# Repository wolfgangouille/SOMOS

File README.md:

# SOMOS
Contains all assets for SOMOS

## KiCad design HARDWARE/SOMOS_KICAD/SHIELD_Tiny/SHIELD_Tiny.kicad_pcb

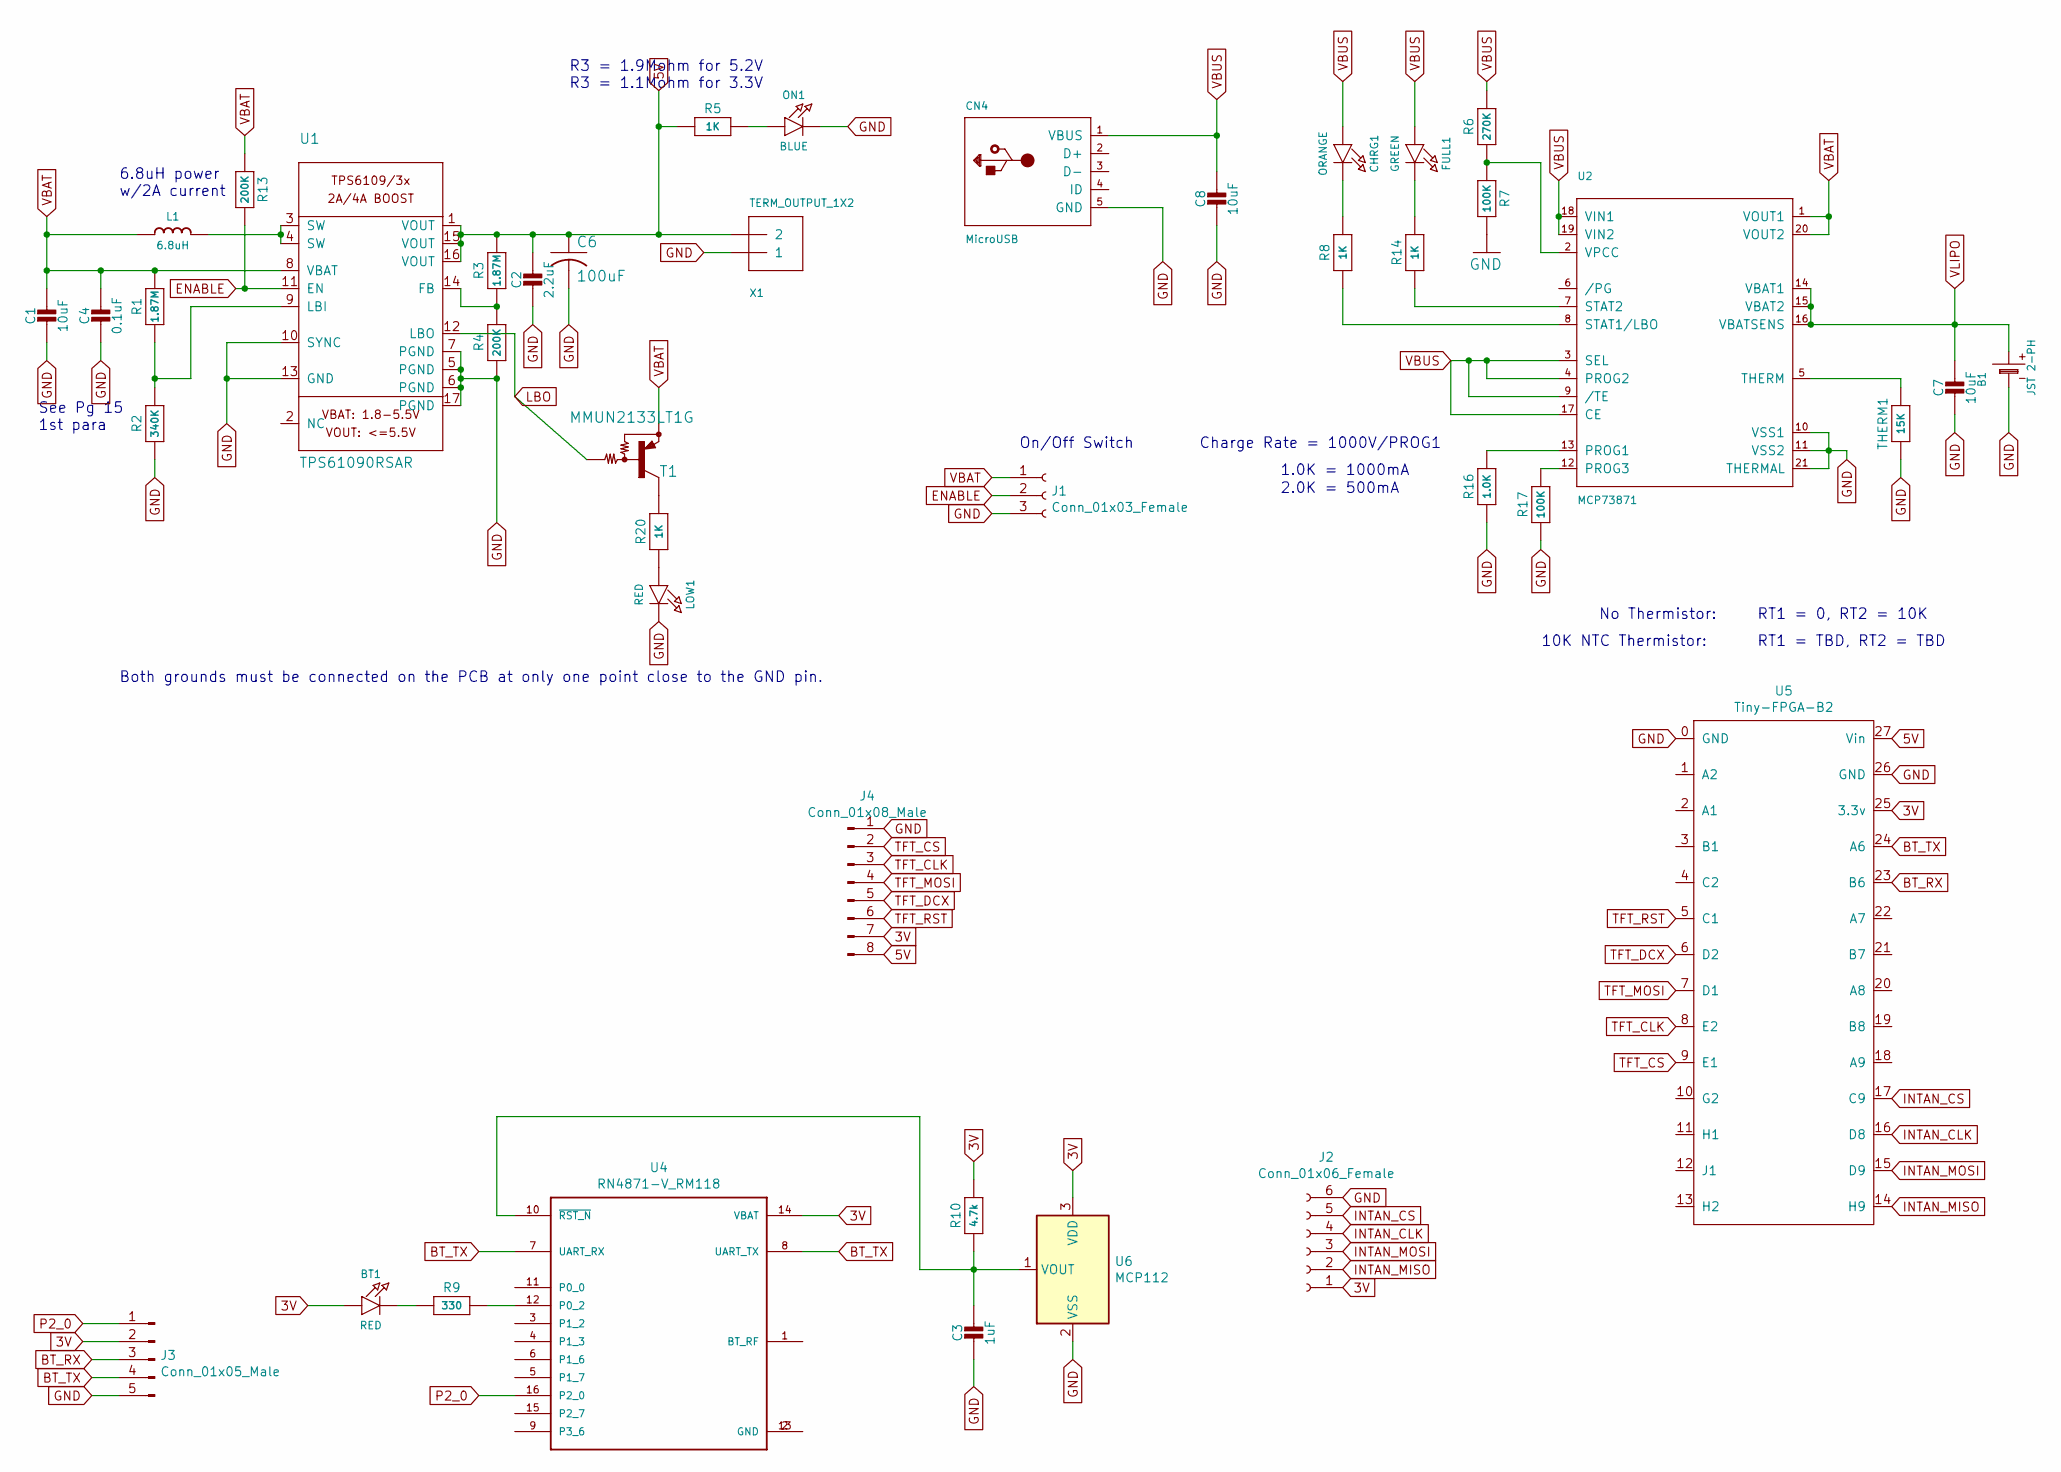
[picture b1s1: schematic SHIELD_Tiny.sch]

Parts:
B1: JST 2-PH; PinHeader_1x02_P2.54mm_Vertical
BT1: RED; LED_0603_1608Metric_Castellated
C1, C7, C8: 10uF; C_0805_2012Metric
C2: 2.2uF; C_0805_2012Metric
C3: 1uF; C_0805_2012Metric
C4: 0.1uF; C_0805_2012Metric
C6: 100uF; C_1210_3225Metric
CHRG1: ORANGE; LED_0603_1608Metric_Castellated
CN4: MicroUSB; USB_Micro-B_GCT_USB3076-30-A
FULL1: GREEN; LED_0603_1608Metric_Castellated
J1: Conn_01x03_Female; PinHeader_1x03_P2.54mm_Vertical
J2: Conn_01x06_Female; JST_SH_SM06B-SRSS-TB_1x06-1MP_P1.00mm_Horizontal
J3: Conn_01x05_Male; JST_SH_SM05B-SRSS-TB_1x05-1MP_P1.00mm_Horizontal
J4: Conn_01x08_Male; JST_SH_SM08B-SRSS-TB_1x08-1MP_P1.00mm_Horizontal
L1: 6.8uH; L_Wuerth_WE-PD2-Typ-MS
LOW1: RED; LED_0603_1608Metric_Castellated
ON1: BLUE; LED_0603_1608Metric_Castellated
R1, R3: 1.87M; R_0805_2012Metric
R2: 340K; R_0805_2012Metric
R4, R13: 200K; R_0805_2012Metric
R5, R8, R14, R20: 1K; R_0603_1608Metric
R6: 270K; R_0805_2012Metric
R7, R17: 100K; R_0603_1608Metric
R9: 330; R_0603_1608Metric
R10: 4.7k; R_0603_1608Metric
R16: 1.0K; R_0603_1608Metric
T1: MMUN2133LT1G; SOT-23
THERM1: 15K; R_0805_2012Metric
U1: TPS61090RSAR; QFN-16-1EP_4x4mm_P0.65mm_EP2.7x2.7mm_ThermalVias
U2: MCP73871; Texas_S-PVQFN-N20_EP2.4x2.4mm_ThermalVias
U4: RN4871-V_RM118; RN4871
U5: Tiny-FPGA-B2; TinyFPGA-BX_TH
U6: MCP112; TO-92_Inline
X1: TERM_OUTPUT_1X2; PinHeader_1x02_P2.54mm_Vertical

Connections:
3V: BT1.1 (A), J2.1, J3.2, J4.7, R10.2, U4.14 (VBAT), U5.25 (3.3v), U6.3 (VDD)
5V: C2.1, C6.1, J4.8, R3.2, R5.1, U1.1 (VOUT), U1.15 (VOUT), U1.16 (VOUT), U5.27 (Vin), X1.2
BT_RX: J3.3, U5.23 (B6)
BT_TX: J3.4, U4.7 (UART_RX), U4.8 (UART_TX), U5.24 (A6)
ENABLE: J1.2, R13.2, U1.11 (EN)
GND: B1.1 (-), C1.2, C2.2, C3.2, C4.2, C6.2, C7.2, C8.2, CN4.5 (GND), CN4.6 (GND), J1.3, J2.6, J3.5, J4.1, LOW1.2 (C), ON1.2 (C), R2.1, R4.1, R7.2, R16.1, R17.1, THERM1.1, U1.5 (PGND), U1.6 (PGND), U1.7 (PGND), U1.10 (SYNC), U1.13 (GND), U1.17 (PGND), U2.10 (VSS1), U2.11 (VSS2), U2.21 (THERMAL), U5.0 (GND), U5.26 (GND), U6.2 (VSS), X1.1
INTAN_CLK: J2.4, U5.16 (D8)
INTAN_CS: J2.5, U5.17 (C9)
INTAN_MISO: J2.2, U5.14 (H9)
INTAN_MOSI: J2.3, U5.15 (D9)
LBO: T1.1 (B), U1.12 (LBO)
unnamed: BT1.2 (C), R9.1
unnamed: C3.1, R10.1, U4.10 (~RST_N~), U6.1 (VOUT)
unnamed: CHRG1.2 (C), R8.2
unnamed: FULL1.2 (C), R14.2
unnamed: L1.2, U1.3 (SW), U1.4 (SW)
unnamed: LOW1.1 (A), R20.1
unnamed: ON1.1 (A), R5.2
unnamed: R1.1, R2.2, U1.9 (LBI)
unnamed: R3.1, R4.2, U1.14 (FB)
unnamed: R6.1, R7.1, U2.2 (VPCC)
unnamed: R8.1, U2.8 (STAT1/LBO)
unnamed: R9.2, U4.12 (P0_2)
unnamed: R14.1, U2.7 (STAT2)
unnamed: R16.2, U2.13 (PROG1)
unnamed: R17.2, U2.12 (PROG3)
unnamed: R20.2, T1.3 (C)
unnamed: THERM1.2, U2.5 (THERM)
unnamed: U4.2 (GND), U4.13 (GND)
P2_0: J3.1, U4.16 (P2_0)
TFT_CLK: J4.3, U5.8 (E2)
TFT_CS: J4.2, U5.9 (E1)
TFT_DCX: J4.5, U5.6 (D2)
TFT_MOSI: J4.4, U5.7 (D1)
TFT_RST: J4.6, U5.5 (C1)
VBAT: C1.1, C4.1, J1.1, L1.1, R1.2, R13.1, T1.2 (E), U1.8 (VBAT), U2.1 (VOUT1), U2.20 (VOUT2)
VBUS: C8.1, CHRG1.1 (A), CN4.1 (VBUS), FULL1.1 (A), R6.2, U2.3 (SEL), U2.4 (PROG2), U2.9 (/TE), U2.17 (CE), U2.18 (VIN1), U2.19 (VIN2)
VLIPO: B1.2 (+), C7.1, U2.14 (VBAT1), U2.15 (VBAT2), U2.16 (VBATSENS)

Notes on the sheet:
On/Off Switch
RT1 = TBD, RT2 = TBD
RT1 = 0, RT2 = 10K
10K NTC Thermistor:
No Thermistor:
2.0K = 500mA
1.0K = 1000mA
Charge Rate = 1000V/PROG1
R3 = 1.9Mohm for 5.2V R3 = 1.1Mohm for 3.3V
6.8uH power w/2A current
See Pg 15 1st para
Both grounds must be connected on the PCB at only one point close to the GND pin.

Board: 2 copper layers, 42 parts (28 on the bottom side), 38 nets, no tracks yet.

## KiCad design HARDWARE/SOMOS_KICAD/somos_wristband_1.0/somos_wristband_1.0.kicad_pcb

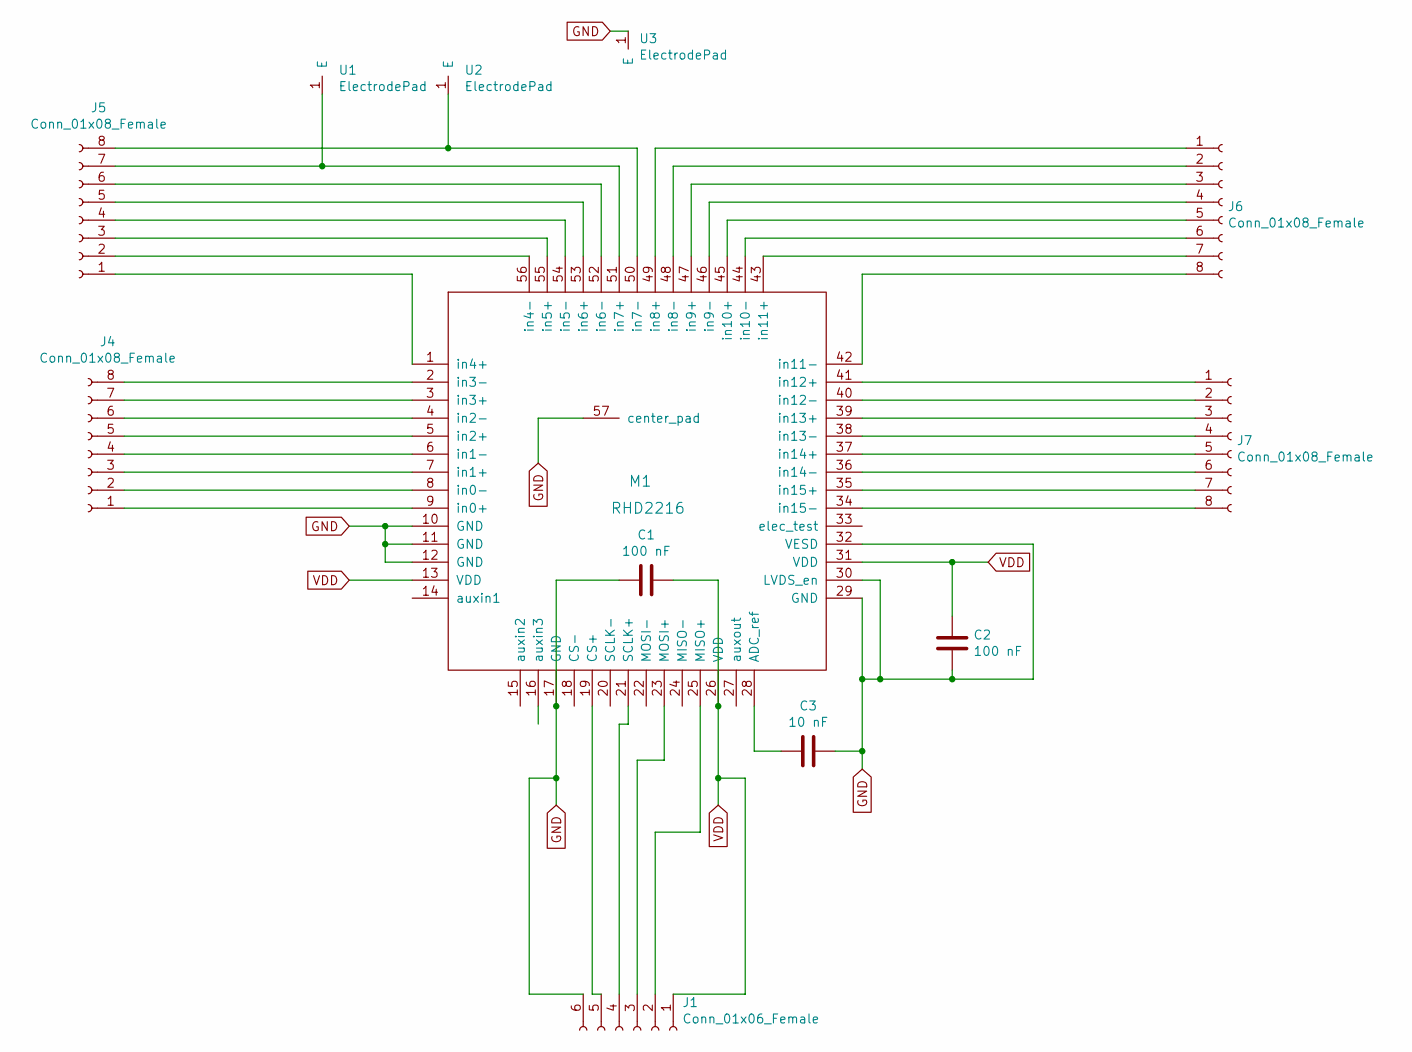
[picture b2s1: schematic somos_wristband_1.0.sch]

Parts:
C1, C2: 100 nF; C_0402_1005Metric
C3: 10 nF; C_0402_1005Metric
J1: Conn_01x06_Female; PinHeader_2x03_P2.54mm_Horizontal
J4, J5, J6, J7: Conn_01x08_Female; PinHeader_1x08_P2.54mm_Vertical
M1: RHD2216; RHD2216_QFN56
U1, U2, U3: ElectrodePad; SOMOS_ELECTRODE

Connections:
GND: C1.2, C2.1, C3.2, J1.6, M1.10 (GND), M1.11 (GND), M1.12 (GND), M1.17 (GND), M1.29 (GND), M1.30 (LVDS_en), M1.32 (VESD), M1.57 (center_pad), U3.1
unnamed: C3.1, M1.28 (ADC_ref)
unnamed: J1.2, M1.25 (MISO+)
unnamed: J1.3, M1.23 (MOSI+)
unnamed: J1.4, M1.21 (SCLK+)
unnamed: J1.5, M1.19 (CS+)
unnamed: J4.1, M1.9 (in0+)
unnamed: J4.2, M1.8 (in0-)
unnamed: J4.3, M1.7 (in1+)
unnamed: J4.4, M1.6 (in1-)
unnamed: J4.5, M1.5 (in2+)
unnamed: J4.6, M1.4 (in2-)
unnamed: J4.7, M1.3 (in3+)
unnamed: J4.8, M1.2 (in3-)
unnamed: J5.1, M1.1 (in4+)
unnamed: J5.2, M1.56 (in4-)
unnamed: J5.3, M1.55 (in5+)
unnamed: J5.4, M1.54 (in5-)
unnamed: J5.5, M1.53 (in6+)
unnamed: J5.6, M1.52 (in6-)
unnamed: J5.7, M1.51 (in7+), U1.1
unnamed: J5.8, M1.50 (in7-), U2.1
unnamed: J6.1, M1.49 (in8+)
unnamed: J6.2, M1.48 (in8-)
unnamed: J6.3, M1.47 (in9+)
unnamed: J6.4, M1.46 (in9-)
unnamed: J6.5, M1.45 (in10+)
unnamed: J6.6, M1.44 (in10-)
unnamed: J6.7, M1.43 (in11+)
unnamed: J6.8, M1.42 (in11-)
unnamed: J7.1, M1.41 (in12+)
unnamed: J7.2, M1.40 (in12-)
unnamed: J7.3, M1.39 (in13+)
unnamed: J7.4, M1.38 (in13-)
unnamed: J7.5, M1.37 (in14+)
unnamed: J7.6, M1.36 (in14-)
unnamed: J7.7, M1.35 (in15+)
unnamed: J7.8, M1.34 (in15-)
VDD: C1.1, C2.2, J1.1, M1.13 (VDD), M1.26 (VDD), M1.31 (VDD)

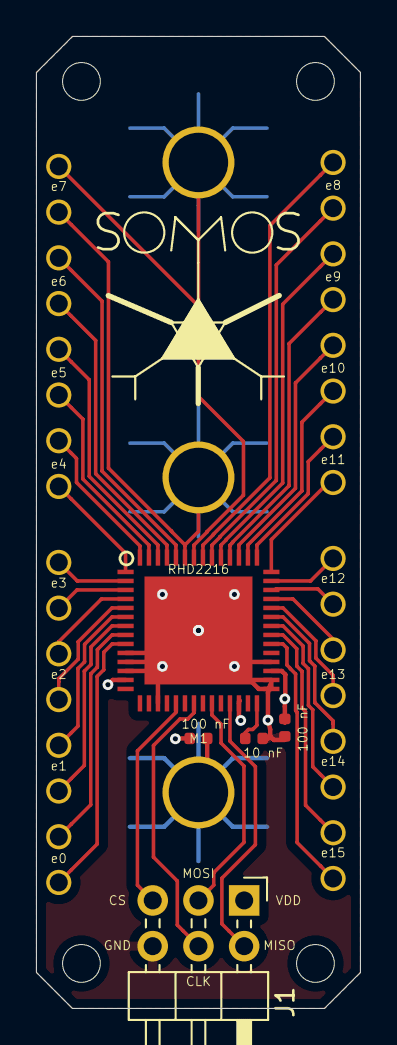
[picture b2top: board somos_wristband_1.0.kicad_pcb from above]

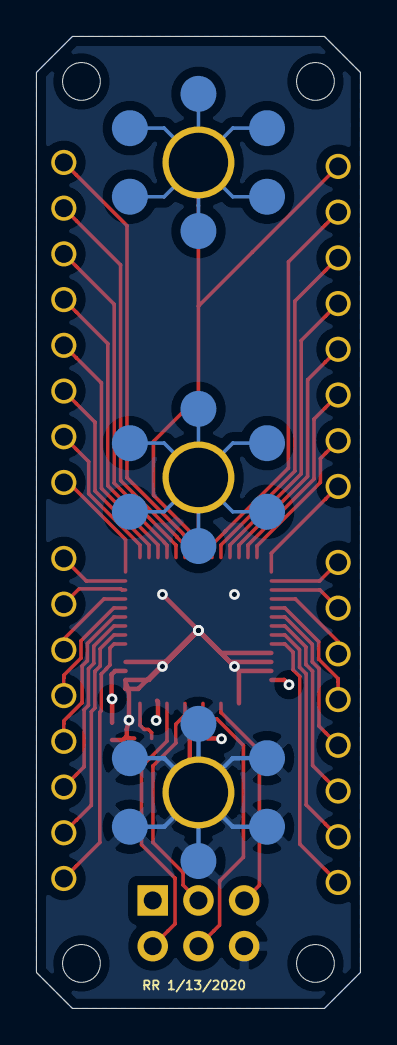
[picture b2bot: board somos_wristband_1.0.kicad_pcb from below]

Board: 4 copper layers, 18.0 x 54.0 mm, 12 parts (3 on the bottom side), 39 nets.

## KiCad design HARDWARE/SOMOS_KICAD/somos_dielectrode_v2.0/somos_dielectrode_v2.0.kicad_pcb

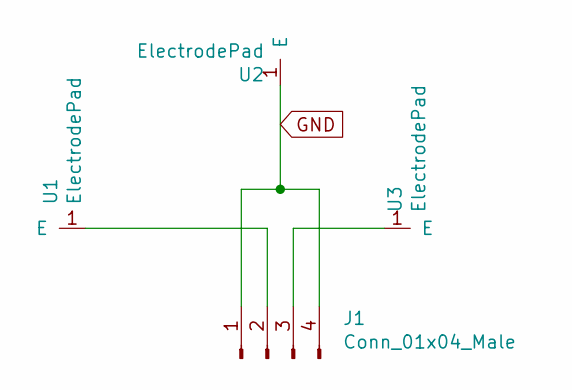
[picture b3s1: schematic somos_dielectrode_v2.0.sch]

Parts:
J1: Conn_01x04_Male; JST_SH_SM04B-SRSS-TB_1x04-DUAL
U1, U2, U3: ElectrodePad; SOMOS_ELECTRODE_2

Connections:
GND: J1.1, J1.4, U2.1
unnamed: J1.2, U1.1
unnamed: J1.3, U3.1

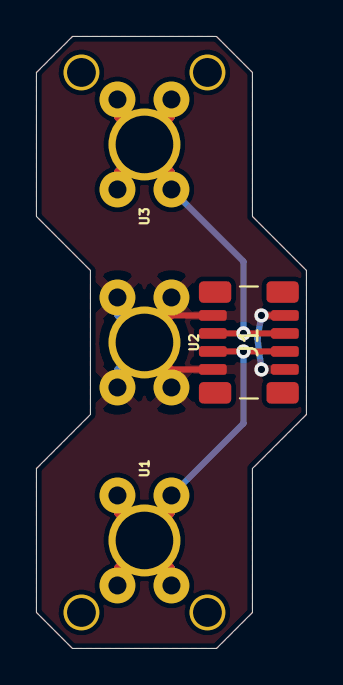
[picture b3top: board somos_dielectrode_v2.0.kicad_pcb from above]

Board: 2 copper layers, 15.0 x 34.0 mm, 4 parts (0 on the bottom side), 3 nets.

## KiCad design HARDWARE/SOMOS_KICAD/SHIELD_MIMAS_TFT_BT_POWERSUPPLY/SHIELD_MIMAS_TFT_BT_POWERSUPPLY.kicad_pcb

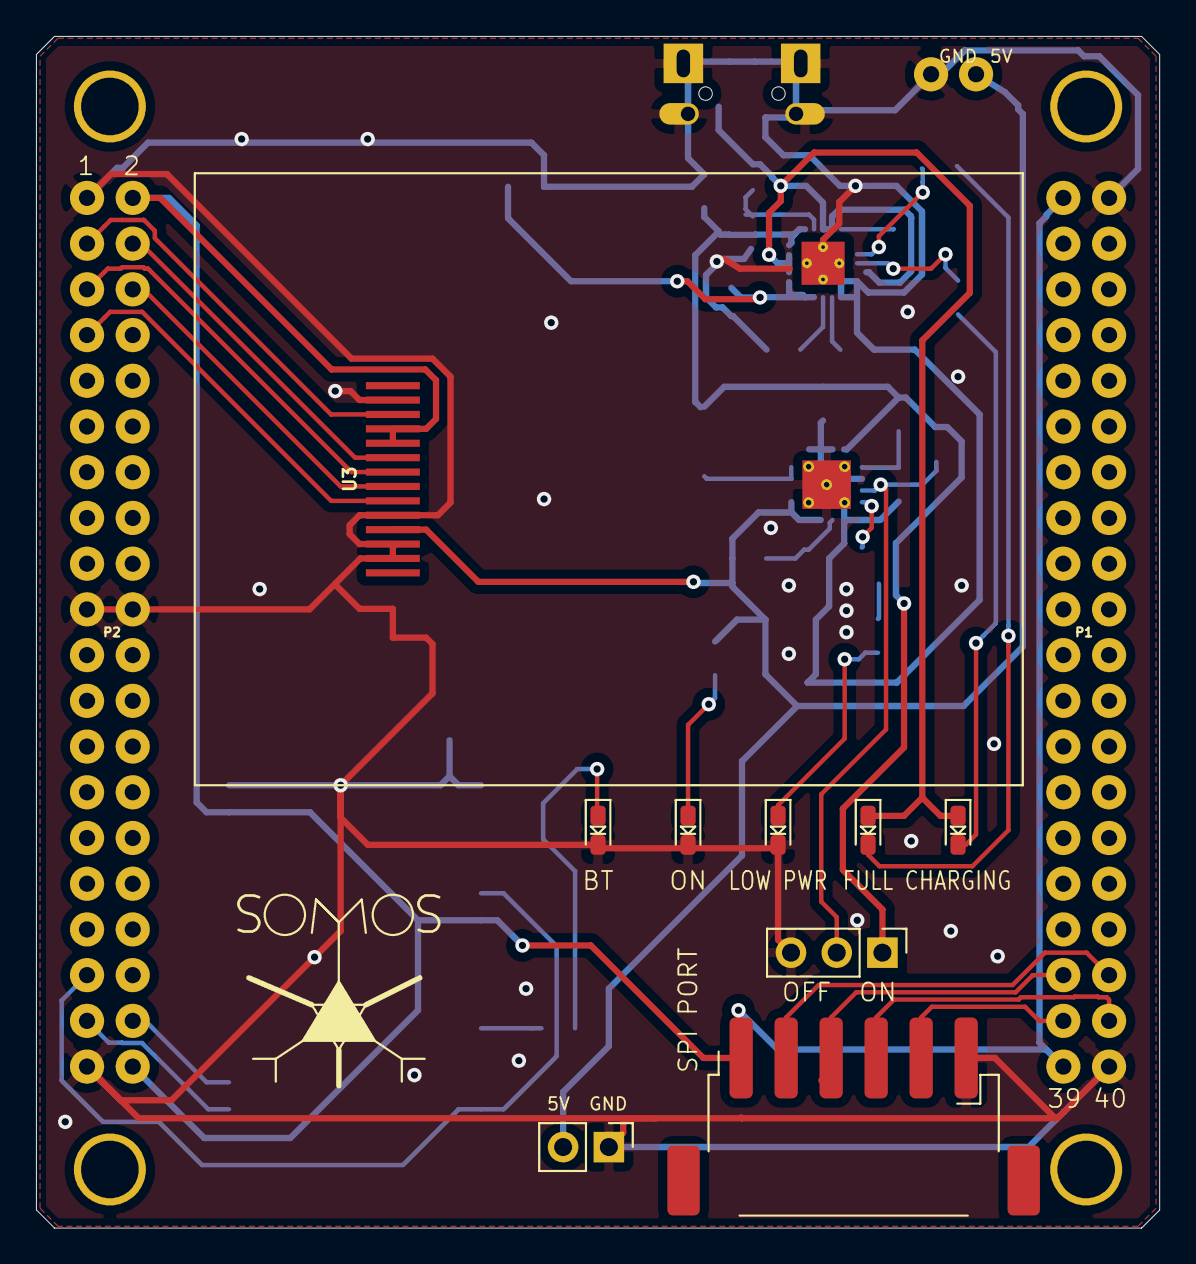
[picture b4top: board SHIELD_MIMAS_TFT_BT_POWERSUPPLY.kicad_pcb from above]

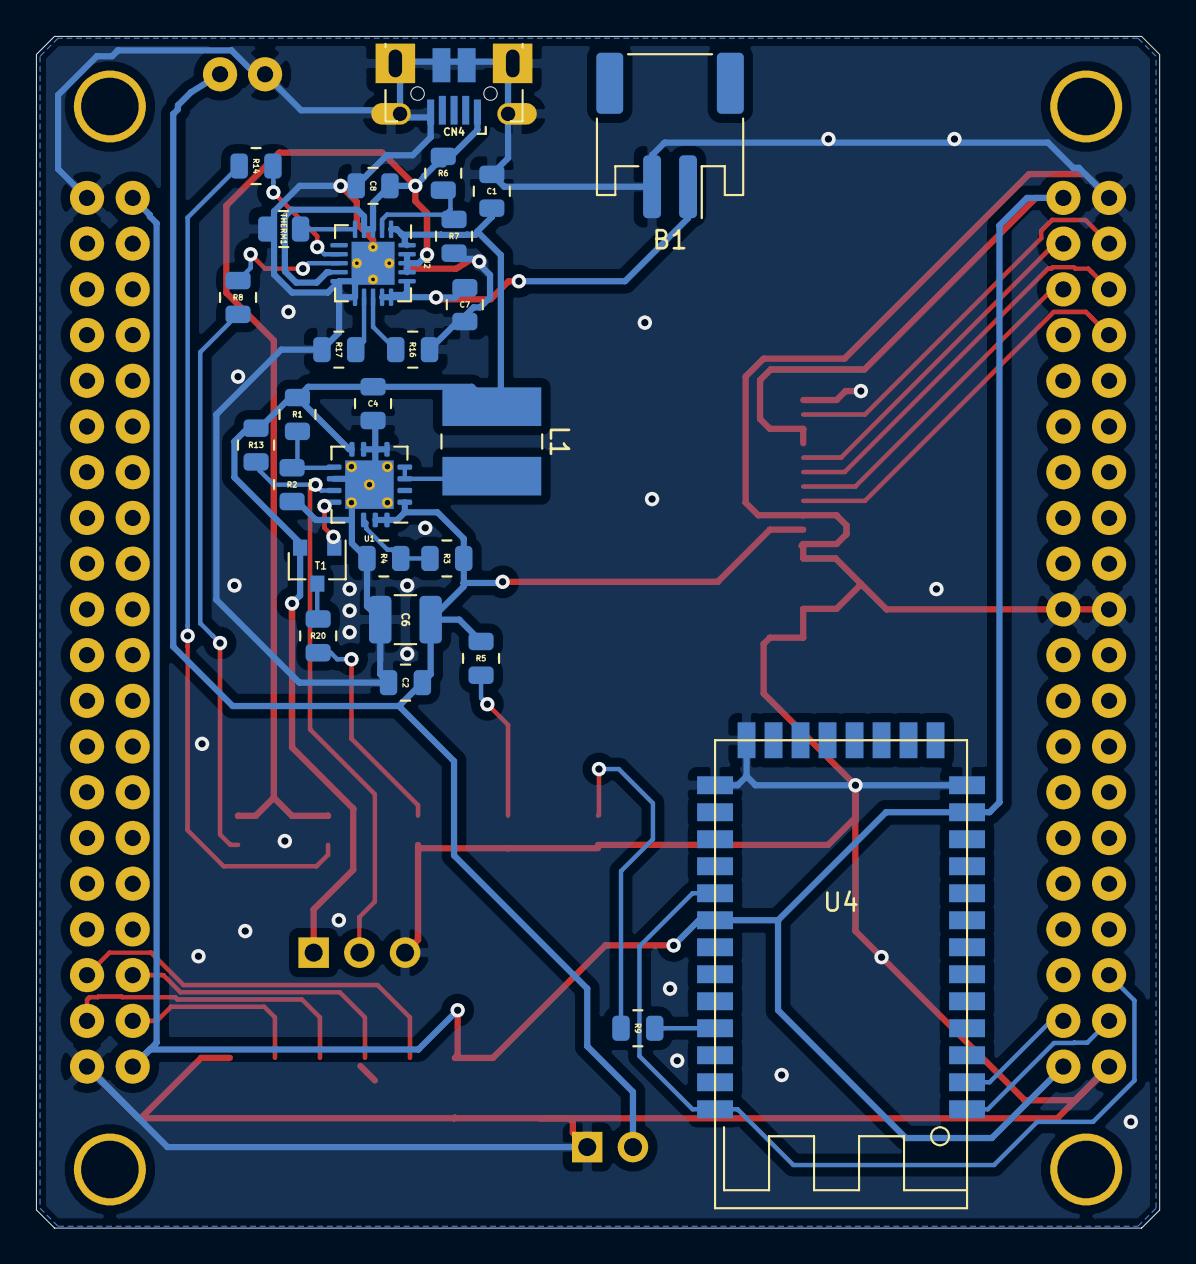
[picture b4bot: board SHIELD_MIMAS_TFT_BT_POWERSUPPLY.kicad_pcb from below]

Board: 2 copper layers, 62.4 x 66.2 mm, 38 parts (28 on the bottom side), 36 nets.

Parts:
5V  GND: TERM_OUTPUT_1X2; PinHeader_1x02_P2.54mm_Vertical
B1: JST 2-PH; JST_PH_S2B-PH-SM4-TB_1x02-1MP_P2.00mm_Horizontal
BT: RED; LED_0603_1608Metric_Castellated
C1, C7, C8: 10uF; C_0805_2012Metric
C2: 2.2uF; C_0805_2012Metric
C4: 0.1uF; C_0805_2012Metric
C6: 100uF; C_1210_3225Metric
CHARGING: ORANGE; LED_0603_1608Metric_Castellated
CN4: MicroUSB; USB_Micro-B_GCT_USB3076-30-A
FULL: GREEN; LED_0603_1608Metric_Castellated
L1: 6.8uH; L_Wuerth_WE-PD2-Typ-MS
LOW PWR: RED; LED_0603_1608Metric_Castellated
OFF  ON: Conn_01x03_Female; PinHeader_1x03_P2.54mm_Vertical
ON: BLUE; LED_0603_1608Metric_Castellated
P1: CONN_40X2; MIMAS_mountingholes
R1, R3: 1.87M; R_0805_2012Metric
R2: 340K; R_0805_2012Metric
R4, R13: 200K; R_0805_2012Metric
R5, R8, R9, R14, R20: 1K; R_0805_2012Metric
R6: 270K; R_0805_2012Metric
R7, R17: 100K; R_0805_2012Metric
R16: 1.0K; R_0805_2012Metric
SPI PORT: Conn_01x06_Female; JST_XH_S6B-XH-SM4
T1: MMUN2133LT1G; SOT-23
THERM1: 15K; R_0805_2012Metric
U1: TPS61090RSAR; QFN-16-1EP_4x4mm_P0.65mm_EP2.7x2.7mm_ThermalVias
U2: MCP73871; Texas_S-PVQFN-N20_EP2.4x2.4mm_ThermalVias
U3: TFT_128x160; TFT128x160
U4: HC-05; HC-05_SMC

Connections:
3V: P1.1-1, P1.1-39, P1.2-2, P1.2-40, SPI PORT.1, U3.10, U3.11, U4.12, U4.27
5V: 5V GND.2, C2.1, C6.1, P1.41, R3.2, R5.1, U1.1, U1.15, U1.16, U3.4
ENABLE: OFF ON.2, R13.2, U1.11
GND: 5V GND.1, B1.1, BT.2, C1.2, C2.2, C4.2, C6.2, C7.2, C8.2, CN4.5, CN4.6, LOW PWR.2, OFF ON.3, ON.2, P1.1-2, P1.1-40, P1.2-1, P1.2-19, P1.2-20, P1.2-39, P1.42, R2.1, R4.1, R7.2, R16.1, R17.1, SPI PORT.6, THERM1.1, U1.5, U1.6, U1.7, U1.10, U1.13, U1.17, U2.10, U2.11, U2.21, U3.2, U3.3, U3.5, U3.13, U4.13, U4.21, U4.22
LBO: T1.1, U1.12
unnamed: BT.1, R9.1
unnamed: CHARGING.2, R8.2
unnamed: FULL.2, R14.2
unnamed: P1.1-36, SPI PORT.2
unnamed: P1.1-35, SPI PORT.3
unnamed: P1.1-38, SPI PORT.4
unnamed: P1.1-37, SPI PORT.5
unnamed: L1.2, U1.3, U1.4
unnamed: LOW PWR.1, R20.1
unnamed: ON.1, R5.2
unnamed: P1.2-3, U3.12
unnamed: P1.2-4, U3.9
unnamed: P1.2-5, U3.8
unnamed: P1.2-6, U3.7
unnamed: P1.2-7, U3.6
unnamed: P1.2-35, U4.26, U4.34
unnamed: P1.2-37, U4.1
unnamed: P1.2-38, U4.2
unnamed: R1.1, R2.2, U1.9
unnamed: R3.1, R4.2, U1.14
unnamed: R6.1, R7.1, U2.2
unnamed: R8.1, U2.8
unnamed: R9.2, U4.31
unnamed: R14.1, U2.7
unnamed: R16.2, U2.13
unnamed: R17.2, U2.12
unnamed: R20.2, T1.3
unnamed: THERM1.2, U2.5
VBAT: C1.1, C4.1, L1.1, OFF ON.1, R1.2, R13.1, T1.2, U1.8, U2.1, U2.20
VBUS: C8.1, CHARGING.1, CN4.1, FULL.1, R6.2, U2.3, U2.4, U2.9, U2.17, U2.18, U2.19
VLIPO: B1.2, C7.1, U2.14, U2.15, U2.16

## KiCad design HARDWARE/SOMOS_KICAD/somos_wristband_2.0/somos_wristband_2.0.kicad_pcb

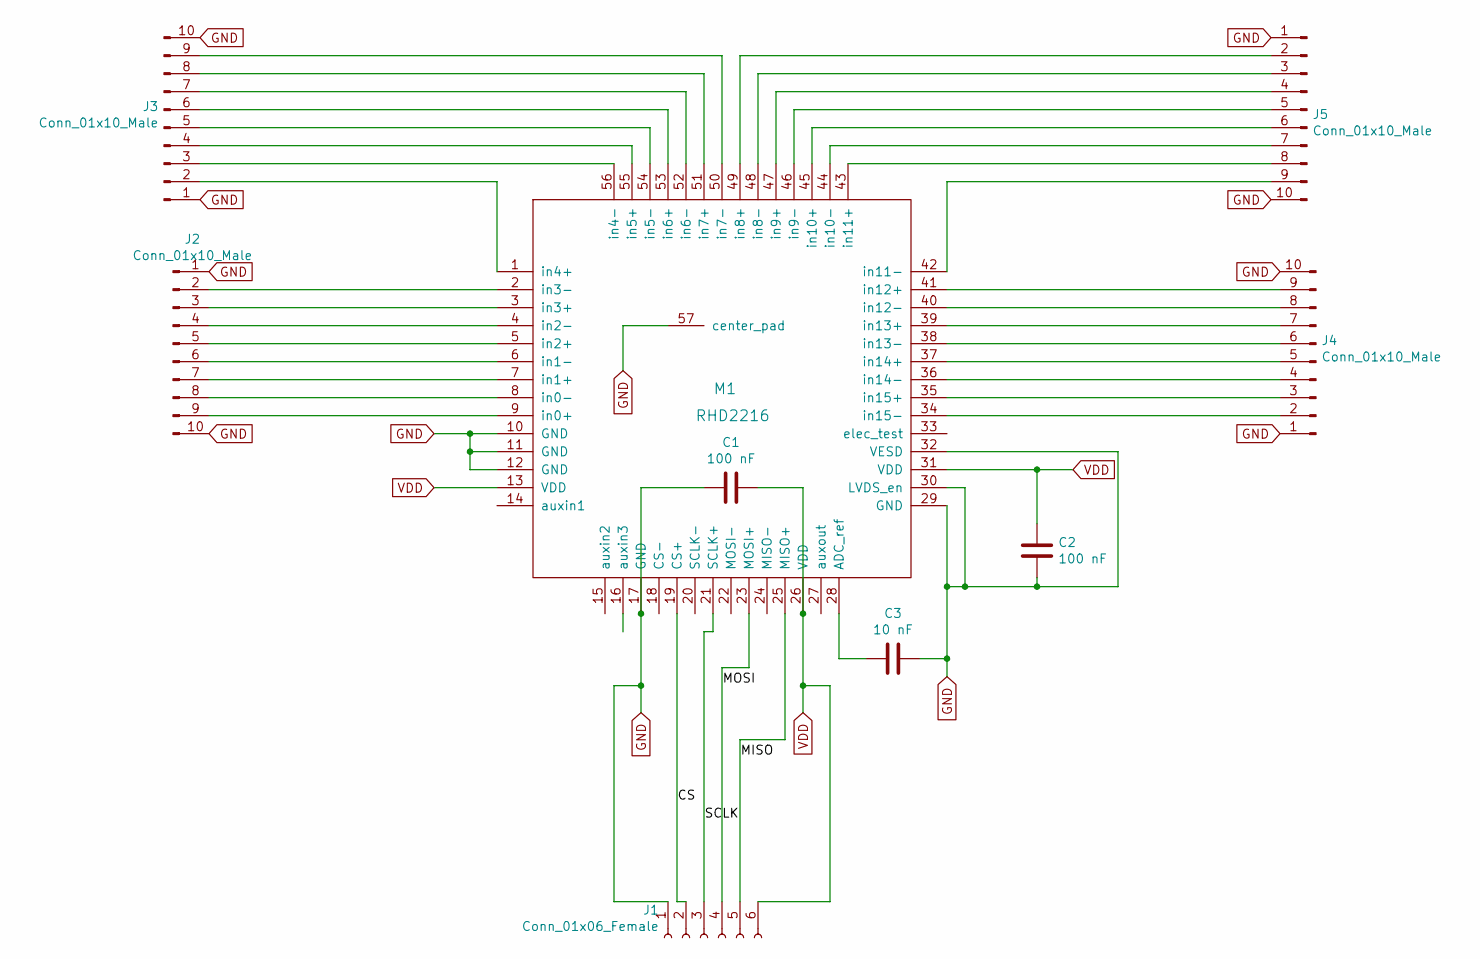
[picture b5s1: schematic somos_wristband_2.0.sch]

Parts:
C1, C2: 100 nF; C_0402_1005Metric
C3: 10 nF; C_0402_1005Metric
J1: Conn_01x06_Female; JST_XH_S6B-XH-SM4
J2, J3, J4, J5: Conn_01x10_Male; JST_SH_SM10B-SRSS-TB_1x10-1MP_P1.00mm_Horizontal
M1: RHD2216; RHD2216_QFN56

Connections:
/CS: J1.2, M1.19 (CS+)
/MISO: J1.5, M1.25 (MISO+)
/MOSI: J1.4, M1.23 (MOSI+)
/SCLK: J1.3, M1.21 (SCLK+)
GND: C1.2, C2.1, C3.2, J1.1, J2.1, J2.10, J3.1, J3.10, J4.1, J4.10, J5.1, J5.10, M1.10 (GND), M1.11 (GND), M1.12 (GND), M1.17 (GND), M1.29 (GND), M1.30 (LVDS_en), M1.32 (VESD), M1.57 (center_pad)
unnamed: C3.1, M1.28 (ADC_ref)
unnamed: J2.2, M1.2 (in3-)
unnamed: J2.3, M1.3 (in3+)
unnamed: J2.4, M1.4 (in2-)
unnamed: J2.5, M1.5 (in2+)
unnamed: J2.6, M1.6 (in1-)
unnamed: J2.7, M1.7 (in1+)
unnamed: J2.8, M1.8 (in0-)
unnamed: J2.9, M1.9 (in0+)
unnamed: J3.2, M1.1 (in4+)
unnamed: J3.3, M1.56 (in4-)
unnamed: J3.4, M1.55 (in5+)
unnamed: J3.5, M1.54 (in5-)
unnamed: J3.6, M1.53 (in6+)
unnamed: J3.7, M1.52 (in6-)
unnamed: J3.8, M1.51 (in7+)
unnamed: J3.9, M1.50 (in7-)
unnamed: J4.2, M1.34 (in15-)
unnamed: J4.3, M1.35 (in15+)
unnamed: J4.4, M1.36 (in14-)
unnamed: J4.5, M1.37 (in14+)
unnamed: J4.6, M1.38 (in13-)
unnamed: J4.7, M1.39 (in13+)
unnamed: J4.8, M1.40 (in12-)
unnamed: J4.9, M1.41 (in12+)
unnamed: J5.2, M1.49 (in8+)
unnamed: J5.3, M1.48 (in8-)
unnamed: J5.4, M1.47 (in9+)
unnamed: J5.5, M1.46 (in9-)
unnamed: J5.6, M1.45 (in10+)
unnamed: J5.7, M1.44 (in10-)
unnamed: J5.8, M1.43 (in11+)
unnamed: J5.9, M1.42 (in11-)
VDD: C1.1, C2.2, J1.6, M1.13 (VDD), M1.26 (VDD), M1.31 (VDD)

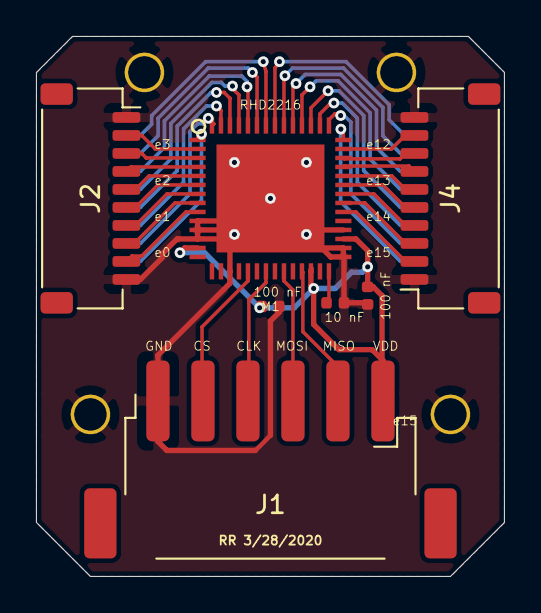
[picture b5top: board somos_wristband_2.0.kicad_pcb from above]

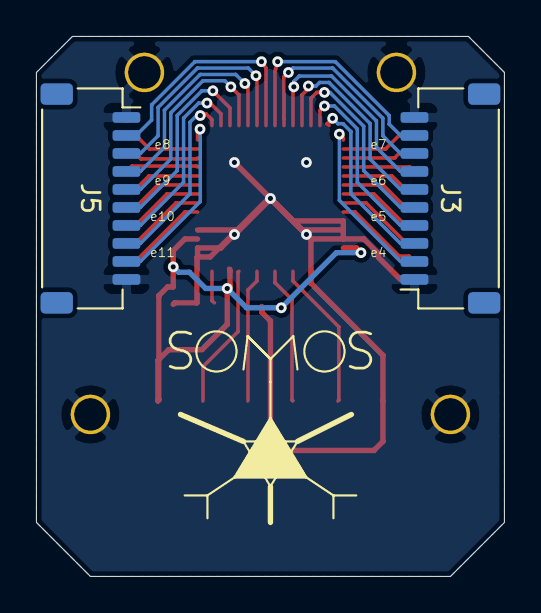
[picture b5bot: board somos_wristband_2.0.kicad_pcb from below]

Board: 4 copper layers, 26.0 x 30.0 mm, 9 parts (2 on the bottom side), 39 nets.

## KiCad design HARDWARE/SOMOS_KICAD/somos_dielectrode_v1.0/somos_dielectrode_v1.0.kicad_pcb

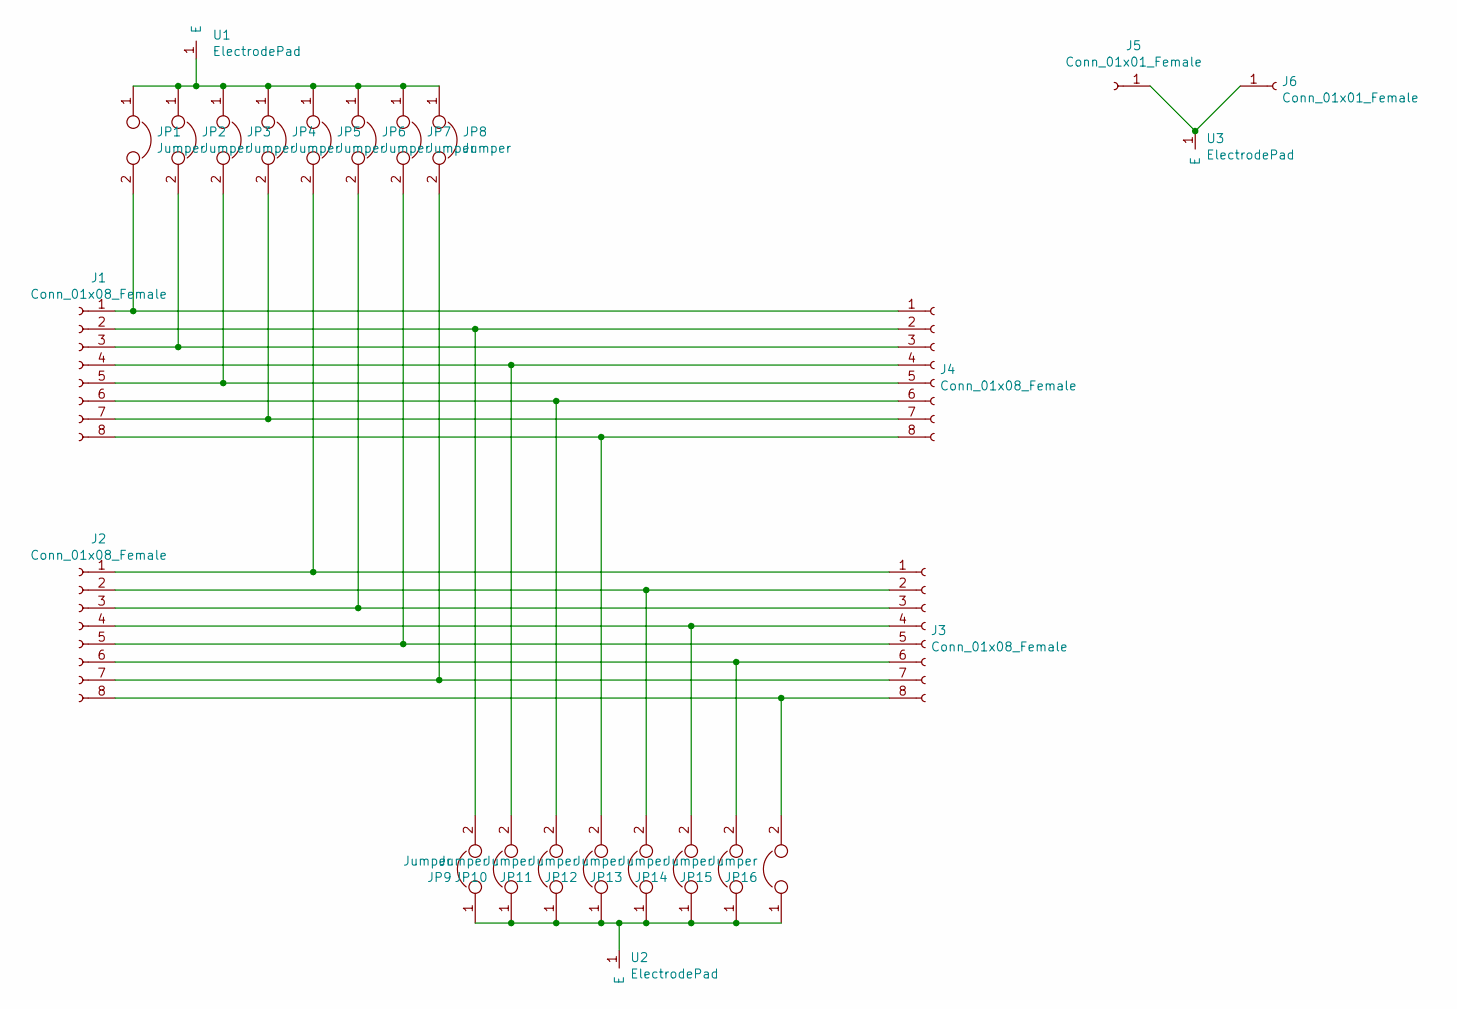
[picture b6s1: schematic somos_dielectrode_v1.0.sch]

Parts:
J1, J2, J3, J4: Conn_01x08_Female; PinHeader_1x08_P2.54mm_Vertical
J5, J6: Conn_01x01_Female; PinHeader_1x01_P2.54mm_Vertical
JP1, JP2, JP3, JP4, JP5, JP6, JP7, JP8, JP9, JP10, JP11, JP12, JP13, JP14, JP15, JP16: Jumper; SolderJumper-2_P1.3mm_Open_RoundedPad1.0x1.5mm
U1, U2, U3: ElectrodePad; SOMOS_ELECTRODE

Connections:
unnamed: J1.1, J4.1, JP1.2
unnamed: J1.2, J4.2, JP9.2
unnamed: J1.3, J4.3, JP2.2
unnamed: J1.4, J4.4, JP10.2
unnamed: J1.5, J4.5, JP3.2
unnamed: J1.6, J4.6, JP11.2
unnamed: J1.7, J4.7, JP4.2
unnamed: J1.8, J4.8, JP12.2
unnamed: J2.1, J3.1, JP5.2
unnamed: J2.2, J3.2, JP13.2
unnamed: J2.3, J3.3, JP6.2
unnamed: J2.4, J3.4, JP14.2
unnamed: J2.5, J3.5, JP7.2
unnamed: J2.6, J3.6, JP15.2
unnamed: J2.7, J3.7, JP8.2
unnamed: J2.8, J3.8, JP16.2
unnamed: J5.1, J6.1, U3.1
unnamed: JP1.1, JP2.1, JP3.1, JP4.1, JP5.1, JP6.1, JP7.1, JP8.1, U1.1
unnamed: JP9.1, JP10.1, JP11.1, JP12.1, JP13.1, JP14.1, JP15.1, JP16.1, U2.1

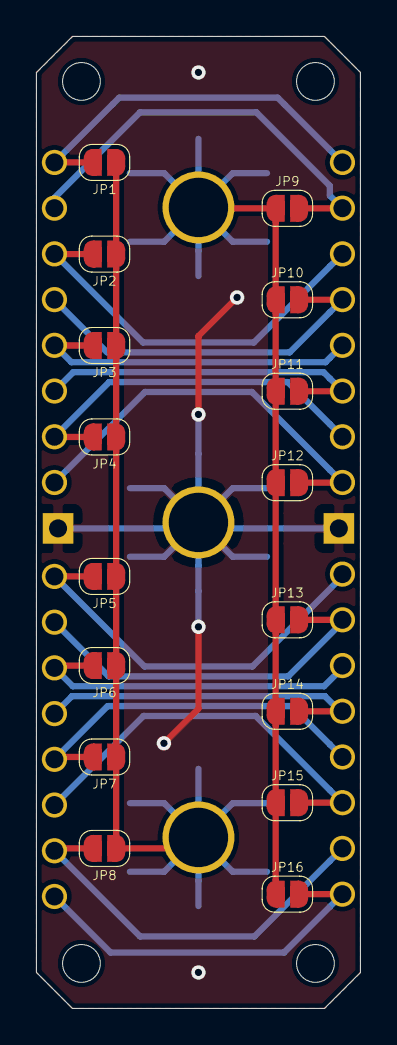
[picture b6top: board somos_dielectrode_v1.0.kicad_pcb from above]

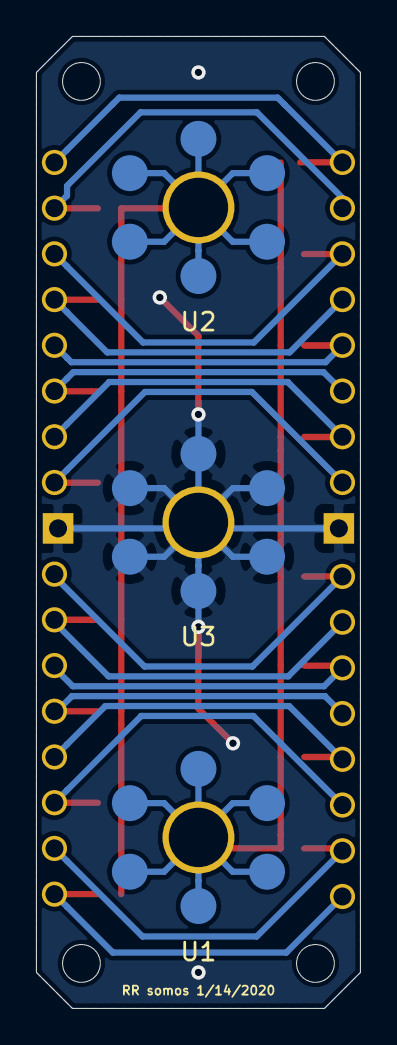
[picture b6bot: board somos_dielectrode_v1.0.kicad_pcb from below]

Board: 2 copper layers, 18.0 x 54.0 mm, 25 parts (3 on the bottom side), 19 nets.

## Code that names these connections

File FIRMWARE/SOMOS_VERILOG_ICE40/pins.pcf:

###############################################################################
#
# TinyFPGA BX constraint file (.pcf)
#
###############################################################################
#
# Copyright (c) 2018, Luke Valenty
# All rights reserved.
#
# Redistribution and use in source and binary forms, with or without
# modification, are permitted provided that the following conditions are met:
#
# 1. Redistributions of source code must retain the above copyright notice, this
#    list of conditions and the following disclaimer.
# 2. Redistributions in binary form must reproduce the above copyright notice,
#    this list of conditions and the following disclaimer in the documentation
#    and/or other materials provided with the distribution.
#
# THIS SOFTWARE IS PROVIDED BY THE COPYRIGHT HOLDERS AND CONTRIBUTORS "AS IS" AND
# ANY EXPRESS OR IMPLIED WARRANTIES, INCLUDING, BUT NOT LIMITED TO, THE IMPLIED
# WARRANTIES OF MERCHANTABILITY AND FITNESS FOR A PARTICULAR PURPOSE ARE
# DISCLAIMED. IN NO EVENT SHALL THE COPYRIGHT OWNER OR CONTRIBUTORS BE LIABLE FOR
# ANY DIRECT, INDIRECT, INCIDENTAL, SPECIAL, EXEMPLARY, OR CONSEQUENTIAL DAMAGES
# (INCLUDING, BUT NOT LIMITED TO, PROCUREMENT OF SUBSTITUTE GOODS OR SERVICES;
# LOSS OF USE, DATA, OR PROFITS; OR BUSINESS INTERRUPTION) HOWEVER CAUSED AND
# ON ANY THEORY OF LIABILITY, WHETHER IN CONTRACT, STRICT LIABILITY, OR TORT
# (INCLUDING NEGLIGENCE OR OTHERWISE) ARISING IN ANY WAY OUT OF THE USE OF THIS
# SOFTWARE, EVEN IF ADVISED OF THE POSSIBILITY OF SUCH DAMAGE.
#
# The views and conclusions contained in the software and documentation are those
# of the authors and should not be interpreted as representing official policies,
# either expressed or implied, of the <project name> project.
#
###############################################################################

####
# TinyFPGA BX information: https://github.com/tinyfpga/TinyFPGA-BX/
####

# Left side of board
set_io --warn-no-port PIN_1 A2 #
set_io --warn-no-port PIN_2 A1 #
set_io --warn-no-port PIN_3 B1
set_io --warn-no-port PIN_4 C2
set_io --warn-no-port TFT_RESX C1
set_io --warn-no-port TFT_DCX D2
set_io --warn-no-port TFT_MOSI D1
set_io --warn-no-port TFT_CLK E2
set_io --warn-no-port TFT_CS E1
set_io --warn-no-port PIN_10 G2
set_io --warn-no-port PIN_11 H1
set_io --warn-no-port PIN_12 J1
set_io --warn-no-port PIN_13 H2 #13

# Right side of board
set_io --warn-no-port INTAN_MISO H9
set_io --warn-no-port INTAN_MOSI D9
set_io --warn-no-port INTAN_CLK D8
set_io --warn-no-port INTAN_CS C9
set_io --warn-no-port PIN_18 A9
set_io --warn-no-port PIN_19 B8
set_io --warn-no-port PIN_20 A8
set_io --warn-no-port PIN_21 B7
set_io --warn-no-port BT_KEY A7
set_io --warn-no-port TX B6
set_io --warn-no-port RX A6

# SPI flash interface on bottom of board
set_io --warn-no-port SPI_SS F7
set_io --warn-no-port SPI_SCK G7
set_io --warn-no-port SPI_IO0 G6
set_io --warn-no-port SPI_IO1 H7
set_io --warn-no-port SPI_IO2 H4
set_io --warn-no-port SPI_IO3 J8

# General purpose pins on bottom of board
set_io --warn-no-port PIN_25 G1
set_io --warn-no-port PIN_26 J3
set_io --warn-no-port PIN_27 J4
set_io --warn-no-port PIN_28 G9
set_io --warn-no-port PIN_29 J9
set_io --warn-no-port PIN_30 E8
set_io --warn-no-port PIN_31 J2

# LED
set_io --warn-no-port LED B3

# USB
set_io --warn-no-port USBP B4
set_io --warn-no-port USBN A4
set_io --warn-no-port USBPU A3

# 16MHz clock
set_io --warn-no-port CLK B2 # input

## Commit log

2020-11-02 first upload
2020-11-02 test
2020-11-02 add freecad assets
2020-11-02 clear old files and update libraries
2020-11-02 Move files
2020-11-02 remove step files
